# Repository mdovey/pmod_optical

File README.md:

# pmod_optical
#### PMOD to Optical (ADAT/SPDIF) Module

PMOD module for interfacing with optical fibres using the JIS F05 connector (up to 16mbps). Typical applications are for digital audio using SPDIF (2 Channel) or ADAT (4/8 Channels).

| PMOD Pin | Name  | Direction | Description                    |
| -------- | ----- | --------- | ------------------------------ |
| 1        | TX    | Out       | Optical transmitter data       |
| 2        | TX_EN | Out       | Enable the optical transmitter |
| 3        | RX    | In        | Optical receiver data          |
| 4        | RX_EN | Out       | Enable the optical receiver    |

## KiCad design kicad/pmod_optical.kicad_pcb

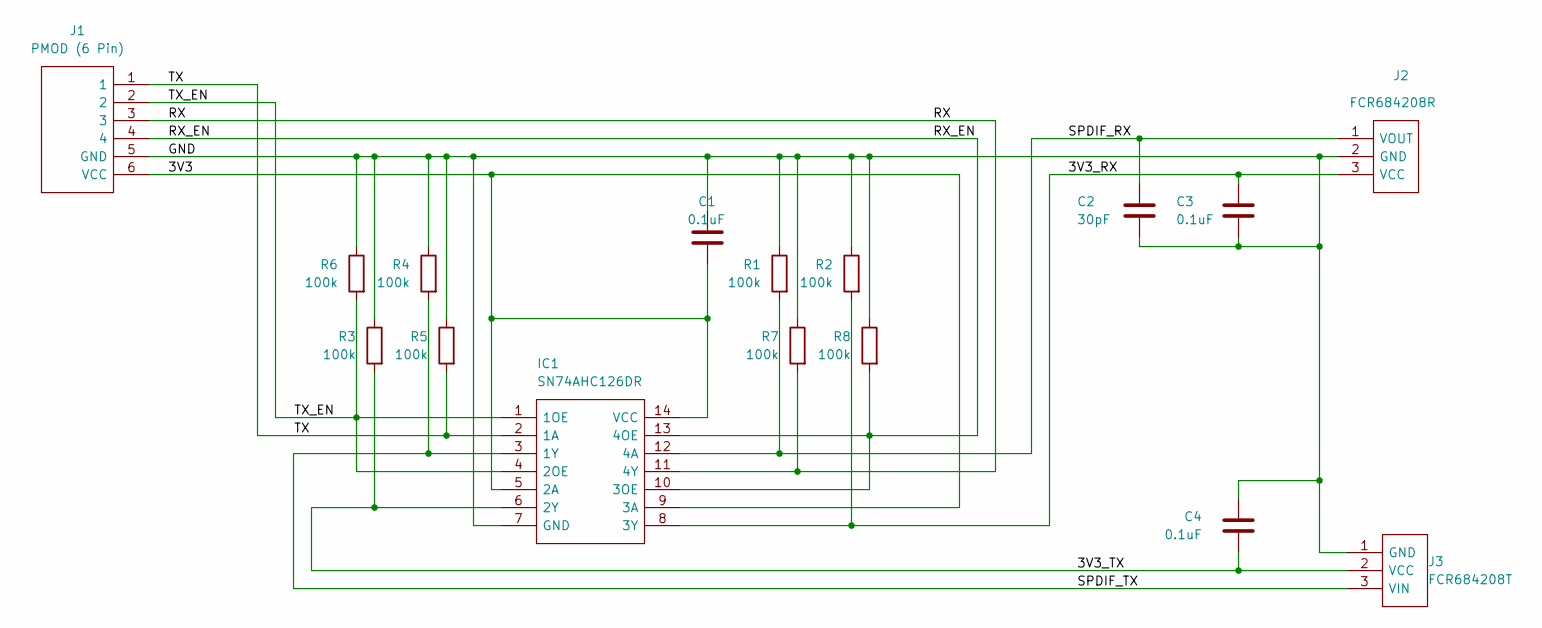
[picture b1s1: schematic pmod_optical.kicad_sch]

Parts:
C1, C3, C4: 0.1uF; C_0805_2012Metric_Pad1.18x1.45mm_HandSolder; MPN 0.1uF 0805 SMD Capacitor
C2: 30pF; C_0805_2012Metric_Pad1.18x1.45mm_HandSolder; MPN 30pf 0805 SMD Capacitor
IC1: SN74AHC126DR; SOIC_SN74AHC126DR; MPN SN74AHC126DR
J1: PMOD (6 Pin); MPN TSW-106-08-L-S-RA
J2: FCR684208R; MPN FCR684208R
J3: FCR684208T; MPN FCR684208T
R1, R2, R3, R4, R5, R6, R7, R8: 100k; R_0805_2012Metric_Pad1.20x1.40mm_HandSolder; MPN 100k ohm 0805 SMD Resistor

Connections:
/3V3: C1.1, IC1.5 (2A), IC1.9 (3A), IC1.14 (VCC), J1.6 (VCC); also elsewhere on the board
/3V3_RX: C3.1, IC1.8 (3Y), J2.3 (VCC), R2.2
/3V3_TX: C4.1, IC1.6 (2Y), J3.2 (VCC), R3.2
/GND: C1.2, C2.2, C3.2, C4.2, IC1.7 (GND), J1.5 (GND), J2.2 (GND), J3.1 (GND), R1.1, R2.1, R3.1, R4.1, R5.1, R6.1, R7.1, R8.1; also elsewhere on the board
/RX: IC1.11 (4Y), J1.3, R7.2; also elsewhere on the board
/RX_EN: IC1.10 (3OE), IC1.13 (4OE), J1.4, R8.2; also elsewhere on the board
/SPDIF_RX: C2.1, IC1.12 (4A), J2.1 (VOUT), R1.2
/SPDIF_TX: IC1.3 (1Y), J3.3 (VIN), R4.2
/TX: IC1.2 (1A), J1.1, R5.2; also elsewhere on the board
/TX_EN: IC1.1 (1OE), IC1.4 (2OE), J1.2, R6.2; also elsewhere on the board

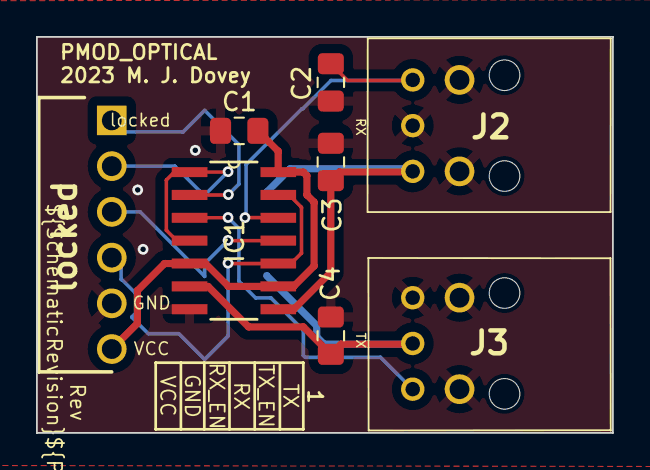
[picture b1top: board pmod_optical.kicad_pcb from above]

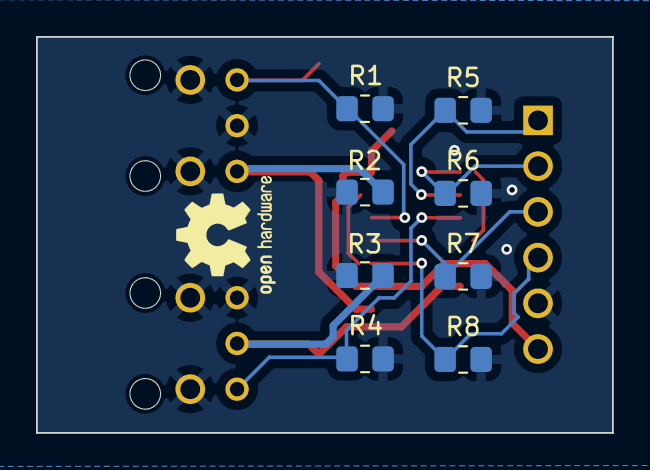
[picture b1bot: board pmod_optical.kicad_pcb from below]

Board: 2 copper layers, 32.0 x 22.0 mm, 16 parts (8 on the bottom side), 10 nets.

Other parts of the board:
locked: PMOD (6 Pin)

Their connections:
/3V3: locked.6 (VCC); also elsewhere on the board
/GND: locked.5 (GND); also elsewhere on the board
/RX: locked.3; also elsewhere on the board
/RX_EN: locked.4; also elsewhere on the board
/TX: locked.1; also elsewhere on the board
/TX_EN: locked.2; also elsewhere on the board

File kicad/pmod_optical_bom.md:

# pmod_optical.kicad_sch BOM

05/08/2023 13:05:41

Generated from schematic by Eeschema 7.0.6

**Component Count:** 16

| Refs | Qty | Component | Description | Manufacturer | MPN | Notes |
| ----- | --- | ---- | ----------- | ---- | ---- | ---- |
| C1, C3, C4 | 3 | 0.1uF | Unpolarized capacitor |  | 0.1uF 0805 SMD Capacitor |  |
| C2 | 1 | 30pF | Unpolarized capacitor |  | 30pf 0805 SMD Capacitor |  |
| IC1 | 1 | SN74AHC126DR | Quadruple Bus Buffer Gates With 3-State Outputs | Texas Instruments | [SN74AHC126DR](https://www.ti.com/lit/gpn/SN74AHC126) | SOIC SMD SN74AHC126DR |
| J1 | 1 | PMOD (6 Pin) | Digilent 6 Pin PMOD Connector | Samtec | [TSW-106-08-L-S-RA](https://suddendocs.samtec.com/catalog_english/tsw_th.pdf)) | 1x6 0.1 Inch pitch right angle pin header |
| J2 | 1 | FCR684208R | Cliff Electronic Components Optical Receiver | Cliff Electronics Components | [FCR684208R](https://www.cliffuk.co.uk/products/optical/FCR684208R.pdf) |  |
| J3 | 1 | FCR684208T | Cliff Electronic Components Optical Transmitter | Cliff Electronics Components | [FCR684208T](https://www.cliffuk.co.uk/products/optical/FCR684208T.pdf) |  |
| R1–8 | 8 | 100k | Resistor |  | 100k ohm 0805 SMD Resistor |  |

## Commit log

2023-07-26 Initial pcb layout
2023-07-27 Added BOM
2023-08-05 Update BOM

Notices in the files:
README.md:
License: GPL v3
